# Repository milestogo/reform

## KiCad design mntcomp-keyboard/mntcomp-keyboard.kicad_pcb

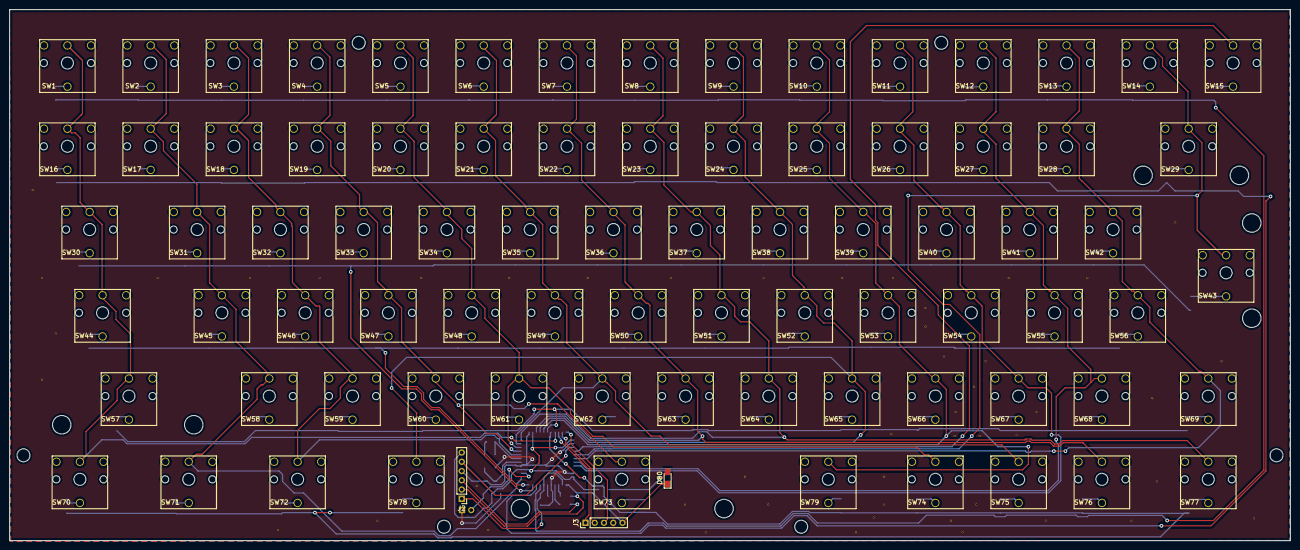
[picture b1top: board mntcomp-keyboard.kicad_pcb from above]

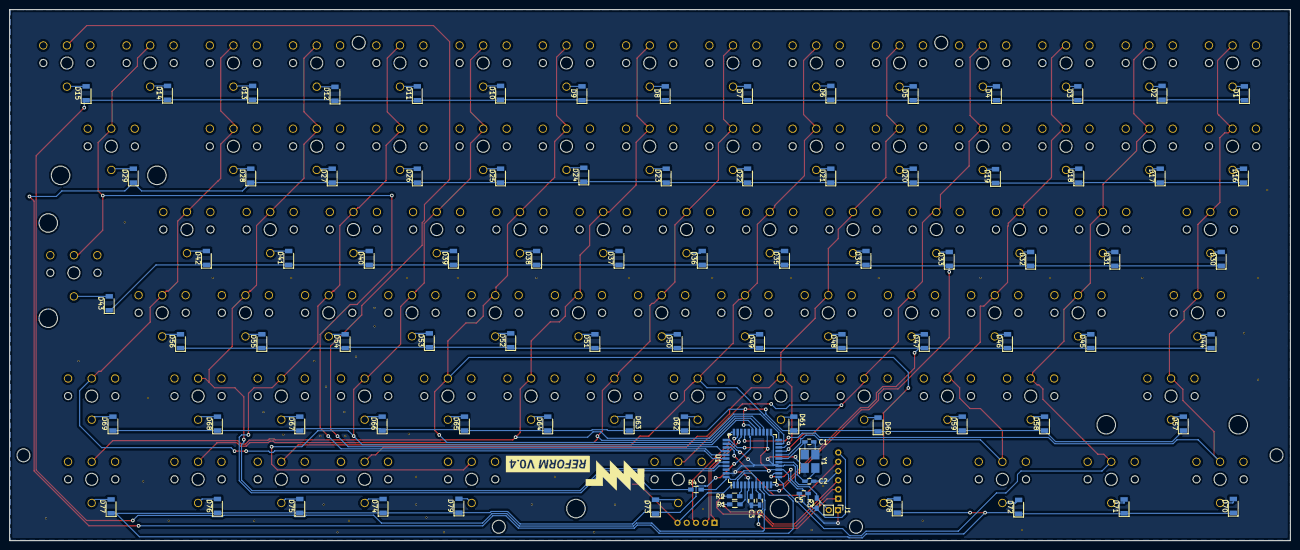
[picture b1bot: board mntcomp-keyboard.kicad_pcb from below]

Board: 2 copper layers, 276.9 x 114.8 mm, 237 parts (91 on the bottom side), 117 nets.

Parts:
C1, C2: 10pF; C_0603_HandSoldering
C3, C4, C5: 1uF; C_0603_HandSoldering
D1, D2, D3, D4, D5, D6, D7, D8, D9, D10, D11, D12, D13, D14, D15, D16, D17, D18, D19, D20, D21, D22, D23, D24, D25, D26, D27, D28, D29, D30, D31, D32, D33, D34, D35, D36, D37, D38, D39, D40, D41, D42, D43, D44, D45, D46, D47, D48, D49, D50, D51, D52, D53, D54, D55, D56, D57, D58, D59, D60, D61, D62, D63, D64, D65, D66, D67, D68, D69, D70, D71, D72, D73, D74, D75, D76, D77, D78, D79: D_Small; D_1206
D80: LED; LED_0805_HandSoldering
J1: Conn_01x02; Pin_Header_Straight_1x02_Pitch2.00mm
J2: Conn_01x06; Pin_Header_Straight_1x06_Pitch2.00mm
J3: Conn_01x05; Pin_Header_Straight_1x05_Pitch2.00mm
MH1, MH2, MH3, MH4, MH5, MH6: Hole; MountingHole_3mm
R: V; VIA-0.4mm
R1, R2: 22; R_0603_HandSoldering
R3: 10k; R_0603_HandSoldering
R4: R_Small; R_0603_HandSoldering
R#2, R#3, R#4, R#5, R#6, R#7, R#8, R#9, R#10, R#11, R#12, R#13, R#14, R#15, R#16, R#17, R#18, R#19, R#20, R#21, R#22, R#23, R#24, R#25, R#26, R#27, R#28, R#29, R#30, R#31, R#32, R#33, R#34, R#35, R#36, R#37, R#38, R#39, R#40, R#41, R#42, R#43, R#44, R#45, R#46, R#47, R#48, R#49, R#50: V; VIA-0.4mm
SH1, SH2, SH3, SH4, SH5, SH6, SH7, SH8: Hole; MountingHole_4mm
SW1, SW2, SW3, SW4, SW5, SW6, SW7, SW8, SW9, SW10, SW11, SW12, SW13, SW14, SW15, SW16, SW17, SW18, SW19, SW20, SW21, SW22, SW23, SW24, SW25, SW26, SW27, SW28, SW29, SW30, SW31, SW32, SW33, SW34, SW35, SW36, SW37, SW38, SW39, SW40, SW41, SW42, SW43, SW44, SW45, SW46, SW47, SW48, SW49, SW50, SW51, SW52, SW53, SW54, SW55, SW56, SW57, SW58, SW59, SW60, SW61, SW62, SW63, SW64, SW65, SW66, SW67, SW68, SW69, SW70, SW71, SW72, SW73, SW74, SW75, SW76, SW77, SW78, SW79: ML; cherry-ml
U1: ATMEGA32U4-AU; TQFP-44_10x10mm_Pitch0.8mm
Y1: 16MHz; Crystal_SMD_3225-4pin_3.2x2.5mm_HandSoldering

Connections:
COL1: SW1.2, SW16.2, SW30.2, SW44.2, SW57.2, SW70.2, U1.30
COL2: SW2.2, SW17.2, SW31.2, SW45.2, SW58.2, SW71.2, U1.12
COL3: SW3.2, SW18.2, SW32.2, SW46.2, SW59.2, SW72.2, U1.18
COL4: SW4.2, SW19.2, SW33.2, SW47.2, SW60.2, SW73.2, U1.19
COL5: SW5.2, SW20.2, SW34.2, SW48.2, SW61.2, SW74.2, U1.20
COL6: SW6.2, SW21.2, SW35.2, SW49.2, SW62.2, SW75.2, U1.21
COL7: SW7.2, SW22.2, SW36.2, SW50.2, SW63.2, SW76.2, U1.25
COL8: SW8.2, SW23.2, SW37.2, SW51.2, SW64.2, SW77.2, U1.22
COL9: SW9.2, SW24.2, SW38.2, SW52.2, SW65.2, SW78.2, U1.26
COL10: SW10.2, SW25.2, SW39.2, SW53.2, SW66.2, SW79.2, U1.27
COL11: SW11.2, SW26.2, SW40.2, SW54.2, SW67.2, U1.41
COL12: SW12.2, SW27.2, SW41.2, SW55.2, SW68.2, U1.40
COL13: SW13.2, SW28.2, SW42.2, SW56.2, SW69.2, U1.39
COL14: SW14.2, SW29.2, SW43.2, U1.38
COL15: SW15.2, U1.37
D+: J2.3, R1.2
D-: J2.2, R2.2
GND: C1.2, C2.2, C3.2, C4.2, C5.2, J1.1, J2.4, J3.4, R.1, R#2.1, R#3.1, R#4.1, R#5.1, R#6.1, R#7.1, R#8.1, R#9.1, R#10.1, R#11.1, R#12.1, R#13.1, R#14.1, R#15.1, R#16.1, R#17.1, R#18.1, R#19.1, R#20.1, R#21.1, R#22.1, R#23.1, R#24.1, R#25.1, R#26.1, R#27.1, R#28.1, R#29.1, R#30.1, R#31.1, R#32.1, R#33.1, R#34.1, R#35.1, R#36.1, R#37.1, R#38.1, R#39.1, R#40.1, R#41.1, R#42.1, R#43.1, R#44.1, R#45.1, R#46.1, R#47.1, R#48.1, R#49.1, R#50.1, U1.5, U1.15, U1.23, U1.35, U1.43, Y1.2, Y1.4
unnamed: C1.1, U1.17, Y1.1
unnamed: C2.1, U1.16, Y1.3
unnamed: C3.1, U1.6
unnamed: D1.2, SW1.4
unnamed: D2.2, SW2.4
unnamed: D3.2, SW3.4
unnamed: D4.2, SW4.4
unnamed: D5.2, SW5.4
unnamed: D6.2, SW6.4
unnamed: D7.2, SW7.4
unnamed: D8.2, SW8.4
unnamed: D9.2, SW9.4
unnamed: D10.2, SW10.4
unnamed: D11.2, SW11.4
unnamed: D12.2, SW12.4
unnamed: D13.2, SW13.4
unnamed: D14.2, SW14.4
unnamed: D15.2, SW15.4
unnamed: D16.2, SW16.4
unnamed: D17.2, SW17.4
unnamed: D18.2, SW18.4
unnamed: D19.2, SW19.4
unnamed: D20.2, SW20.4
unnamed: D21.2, SW21.4
unnamed: D22.2, SW22.4
unnamed: D23.2, SW23.4
unnamed: D24.2, SW24.4
unnamed: D25.2, SW25.4
unnamed: D26.2, SW26.4
unnamed: D27.2, SW27.4
unnamed: D28.2, SW28.4
unnamed: D29.2, SW29.4
unnamed: D30.2, SW30.4
unnamed: D31.2, SW31.4
unnamed: D32.2, SW32.4
unnamed: D33.2, SW33.4
unnamed: D34.2, SW34.4
unnamed: D35.2, SW35.4
unnamed: D36.2, SW36.4
unnamed: D37.2, SW37.4
unnamed: D38.2, SW38.4
unnamed: D39.2, SW39.4
unnamed: D40.2, SW40.4
unnamed: D41.2, SW41.4
unnamed: D42.2, SW42.4
unnamed: D43.2, SW43.4
unnamed: D44.2, SW44.4
unnamed: D45.2, SW45.4
unnamed: D46.2, SW46.4
unnamed: D47.2, SW47.4
unnamed: D48.2, SW48.4
unnamed: D49.2, SW49.4
unnamed: D50.2, SW50.4
unnamed: D51.2, SW51.4
unnamed: D52.2, SW52.4
unnamed: D53.2, SW53.4
unnamed: D54.2, SW54.4
unnamed: D55.2, SW55.4
unnamed: D56.2, SW56.4
unnamed: D57.2, SW57.4
unnamed: D58.2, SW58.4
unnamed: D59.2, SW59.4
unnamed: D60.2, SW60.4
unnamed: D61.2, SW61.4
unnamed: D62.2, SW62.4
unnamed: D63.2, SW63.4
unnamed: D64.2, SW64.4
unnamed: D65.2, SW65.4
unnamed: D66.2, SW66.4
unnamed: D67.2, SW67.4
unnamed: D68.2, SW68.4
unnamed: D69.2, SW69.4
unnamed: D70.2, SW70.4
unnamed: D71.2, SW71.4
unnamed: D72.2, SW72.4
unnamed: D73.2, SW73.4
unnamed: D74.2, SW74.4
unnamed: D75.2, SW75.4
unnamed: D76.2, SW76.4
unnamed: D77.2, SW77.4
unnamed: D78.2, SW78.4
unnamed: D79.2, SW79.4
unnamed: D80.1, J3.5, U1.1
unnamed: D80.2, R4.1
unnamed: J3.1, U1.31
unnamed: J3.2, U1.32
unnamed: J3.3, U1.33
unnamed: R1.1, U1.4
unnamed: R2.1, U1.3
PWRON: J2.5, U1.36
RAWVCC: C5.1, J2.6, R3.1, R4.2, U1.14, U1.24, U1.34, U1.44
RESET: J1.2, R3.2, U1.13
ROW1: D1.1, D2.1, D3.1, D4.1, D5.1, D6.1, D7.1, D8.1, D9.1, D10.1, D11.1, D12.1, D13.1, D14.1, D15.1, U1.8
ROW2: D16.1, D17.1, D18.1, D19.1, D20.1, D21.1, D22.1, D23.1, D24.1, D25.1, D26.1, D27.1, D28.1, D29.1, U1.9
ROW3: D30.1, D31.1, D32.1, D33.1, D34.1, D35.1, D36.1, D37.1, D38.1, D39.1, D40.1, D41.1, D42.1, D43.1, U1.10
ROW4: D44.1, D45.1, D46.1, D47.1, D48.1, D49.1, D50.1, D51.1, D52.1, D53.1, D54.1, D55.1, D56.1, U1.11
ROW5: D57.1, D58.1, D59.1, D60.1, D61.1, D62.1, D63.1, D64.1, D65.1, D66.1, D67.1, D68.1, D69.1, U1.28
ROW6: D70.1, D71.1, D72.1, D73.1, D74.1, D75.1, D76.1, D77.1, D78.1, D79.1, U1.29
UVCC: C4.1, J2.1, U1.2, U1.7

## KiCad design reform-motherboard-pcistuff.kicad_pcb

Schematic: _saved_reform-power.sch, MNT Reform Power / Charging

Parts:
BT1: Battery_Cell; SHDR4W90P500X350_2X2_865X1100X800P
C2, C27: 4.7uF; C_0603_HandSoldering
C3, C25, C28, C34: 10uF; C_0603_HandSoldering
C18, C19, C20, C21, C22: 22uF; CP_Elec_4x5.8
C23: 47uF; CP_Elec_4x5.8
C24: 0.1uF; C_0603_HandSoldering
C26, C29: 1uF; C_0603_HandSoldering
C33: 4.7uF; C_0805_HandSoldering
D1, D4: D_Schottky; D_SOD-323_HandSoldering
D3: LED_CHRG; LED_0805_HandSoldering
J6: Barrel_Jack; SWC_RAPC712X
J22: Conn_PWRON; Pin_Header_Straight_1x02_Pitch2.54mm
L1: 1 uH; Inductor_Taiyo-Yuden_MD-4040
L2: 18 uH; Inductor_1212
R2: 1.15k; R_0603_HandSoldering
R3: 1k; R_0603_HandSoldering
R4: 5.1k; R_0603_HandSoldering
R5, R14: 2.4k; R_0603_HandSoldering
R7, R8, R9, R10, R15: 0; R_0603_HandSoldering
R11: 10k; R_0603_HandSoldering
R13: 2.1k; R_0603_HandSoldering
TP1: TEST_BAT; Measurement_Point_Round-SMD-Pad_Big
TP2: TEST_5V; Measurement_Point_Round-SMD-Pad_Big
TP3: TEST_3V3; Measurement_Point_Round-SMD-Pad_Big
TP5: TEST_2V5; Measurement_Point_Round-SMD-Pad_Big
TP11: PWRMON_ALERT; Measurement_Point_Round-SMD-Pad_Big
TP12: TEST_1V5; Measurement_Point_Round-SMD-Pad_Big
U2: MCP73123T-22SI/MF; SON50P300X300X100-11N; Digi-Key_Part_Number MCP73123T-22SI/MF-ND
U3: TPS61235RWLR; CONV_TPS61235RWLR
U4: AP1501A-33K5G-13; DPAK171P1524X485-6N
U5: SN74LVC1G14DBVR; SOT95P280X145-5N
U6, U11: TPS74801DRCR; SON50P300X300X100-11N
U7: INA260AIPW; SOP65P640X120-16N

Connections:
+1V5: C34.1, R13.1, U11.9, U11.10; also elsewhere on the board
+2V5: C28.1, R4.1, R11.1, U6.9, U6.10; also elsewhere on the board
+3V3: C22.1, C23.1, L2.2, R8.2, TP3.1, U4.4; also elsewhere on the board
+5V: C18.1, C19.1, C20.1, C21.1, C26.1, C29.1, R10.2, TP2.1, U3.6, U3.9, U4.1, U5.5, U6.1, U6.2, U11.1, U11.2; also elsewhere on the board
GND: BT1.2, C2.2, C3.2, C18.2, C19.2, C20.2, C21.2, C22.2, C23.2, C24.2, C25.2, C26.2, C27.2, C28.2, C29.2, C33.2, C34.2, D3.2, D4.2, J6.2, R2.1, R5.2, R14.2, U2.8, U2.9, U2.11, U3.1, U3.4, U3.5, U3.8, U4.3, U4.6, U5.3, U6.6, U6.7, U6.11, U7.4, U7.6, U7.11, U7.13, U11.6, U11.7, U11.11; also elsewhere on the board
I2C3_SCL: U7.9; also elsewhere on the board
I2C3_SDA: U7.8; also elsewhere on the board
JACK_SENSE: J6.3
unnamed: BT1.1, C2.1, D1.2, TP1.1, U2.3, U2.4
unnamed: C3.1, J22.1, L1.1, U3.3, U7.14, U7.15, U7.16
unnamed: C24.1, R7.1, U7.5, U7.10
unnamed: C25.1, D1.1, J6.1, R7.2, U2.1, U2.2, U7.1, U7.2, U7.3, U7.12
unnamed: C27.1, U6.4
unnamed: C33.1, U11.4
unnamed: D3.1, R3.1
unnamed: D4.1, L2.1, U4.2
unnamed: L1.2, U3.2
unnamed: R2.2, U2.10
unnamed: R3.2, U2.7
unnamed: R4.2, R5.1, TP5.1, U6.8
unnamed: R9.1, U6.5
unnamed: R13.2, R14.1, TP12.1, U11.8
unnamed: R15.1, U11.5
unnamed: TP11.1, U7.7
unnamed: U4.5, U5.4
POK_1V5: U11.3; also elsewhere on the board
POK_1V5_MODULE: R9.2; also elsewhere on the board
POK_2V5: R11.2, U5.2, U6.3
POK_3V3: R8.1, R15.2; also elsewhere on the board
POK_5V: R10.1; also elsewhere on the board
PWRON: J22.2, U3.7

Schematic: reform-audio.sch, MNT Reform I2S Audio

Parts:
C55, C56, C57, C58, C59, C61, C63: 0.1uF; C_0603_HandSoldering
C60, C62, C64, C65: 1uF; C_0603_HandSoldering
J16: Conn_LineIn; Pin_Header_Straight_1x03_Pitch2.00mm
J17: Conn_LineOut; Pin_Header_Straight_1x03_Pitch2.00mm
J18: TRRS; SJ-43516-SMT
R31: 2.2k; R_0603_HandSoldering
U10: SGTL5000XNAA3; QFN50P500X500X100-33N

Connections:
+1V5: C59.2, C61.2, U10.5, U10.30; also elsewhere on the board
+3V3: C63.2, U10.20; also elsewhere on the board
AUD4_CLK: U10.21; also elsewhere on the board
AUD4_RXD: U10.25; also elsewhere on the board
AUD4_TXC: U10.24; also elsewhere on the board
AUD4_TXD: U10.26; also elsewhere on the board
AUD4_TXFS: U10.23; also elsewhere on the board
GND: C55.1, C56.1, C58.1, C59.1, C61.1, C63.1, J16.3, J17.3, U10.1, U10.3, U10.7, U10.31, U10.32, U10.EXP; also elsewhere on the board
I2C3_SCL: U10.29; also elsewhere on the board
I2C3_SDA: U10.27; also elsewhere on the board
unnamed: C55.2, U10.10
unnamed: C56.2, R31.2, U10.16
unnamed: C57.1, U10.15
unnamed: C57.2, J18.4, R31.1
unnamed: C58.2, U10.18
unnamed: C60.1, U10.14
unnamed: C60.2, J16.1
unnamed: C62.1, U10.13
unnamed: C62.2, J16.2
unnamed: C64.1, J17.2
unnamed: C64.2, U10.11
unnamed: C65.1, J17.1
unnamed: C65.2, U10.12
unnamed: J18.1, U10.6
unnamed: J18.2, U10.2
unnamed: J18.3, U10.4

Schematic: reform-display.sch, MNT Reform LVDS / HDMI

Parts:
C67, C68: 10uF; C_0603_HandSoldering
C69, C70, C71, C72, C73: 0.1uF; C_0603_HandSoldering
D6: D_Schottky; D_SOD-323_HandSoldering
J13: Conn_HDMI; 685119134923
J14: Conn_LVDS; Pin_Header_Angled_2x10_Pitch2.00mm
J26: Conn_Backlight; Pin_Header_Angled_1x06_Pitch2.00mm
R35: R0; R_0603_HandSoldering
R36: 47k; R_0603_HandSoldering
R37: 27k; R_0603_HandSoldering
R38, R39: 4.99k; R_0603_HandSoldering
R40: 15k; R_0603_HandSoldering
U14: CM2020-00TR; TSSOP50P640X120-38N

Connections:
+3V3: C68.1, C69.1, D6.2, J14.1, J14.2, J14.3, R35.2, U14.2; also elsewhere on the board
+5V: C67.1, C70.1, J26.1, U14.1; also elsewhere on the board
GND: C67.2, C68.2, C69.2, C70.2, C71.2, C72.2, C73.2, J13.2, J13.5, J13.8, J13.11, J13.17, J14.5, J14.6, J26.6, R40.2, U14.3, U14.5, U14.8, U14.11, U14.14, U14.25, U14.28, U14.31, U14.34, U14.36; also elsewhere on the board
HDMI_CEC_IN: U14.16; also elsewhere on the board
HDMI_CLK_N: J13.12, U14.15, U14.24; also elsewhere on the board
HDMI_CLK_P: J13.10, U14.13, U14.26; also elsewhere on the board
HDMI_D0_N: J13.9, U14.12, U14.27; also elsewhere on the board
HDMI_D0_P: J13.7, U14.10, U14.29; also elsewhere on the board
HDMI_D1_N: J13.6, U14.9, U14.30; also elsewhere on the board
HDMI_D1_P: J13.4, U14.7, U14.32; also elsewhere on the board
HDMI_D2_N: J13.3, U14.6, U14.33; also elsewhere on the board
HDMI_D2_P: J13.1, U14.4, U14.35; also elsewhere on the board
HDMI_HPD: R36.1, U14.19; also elsewhere on the board
I2C1_SCL: U14.17; also elsewhere on the board
I2C1_SDA: U14.18; also elsewhere on the board
LVDS0_CLK_N: J14.15; also elsewhere on the board
LVDS0_CLK_P: J14.16; also elsewhere on the board
LVDS0_PWM: J26.4; also elsewhere on the board
LVDS0_TX0_N: J14.7; also elsewhere on the board
LVDS0_TX0_P: J14.8; also elsewhere on the board
LVDS0_TX1_N: J14.9; also elsewhere on the board
LVDS0_TX1_P: J14.10; also elsewhere on the board
LVDS0_TX2_N: J14.11; also elsewhere on the board
LVDS0_TX2_P: J14.12; also elsewhere on the board
LVDS0_TX3_N: J14.19; also elsewhere on the board
LVDS0_TX3_P: J14.20; also elsewhere on the board
unnamed: C71.1, U14.37
unnamed: C72.1, J13.19, R40.1, U14.20
unnamed: C73.1, J13.18, R36.2, R38.2, R39.2, U14.38
unnamed: D6.1, R37.2
unnamed: J13.13, R37.1, U14.23
unnamed: J13.15, R38.1, U14.22
unnamed: J13.16, R39.1, U14.21
unnamed: J26.3, R35.1

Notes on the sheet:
LCD Screen
HDMI

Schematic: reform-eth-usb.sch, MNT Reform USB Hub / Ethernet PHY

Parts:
C13, C14, C15, C16, C17, C38, C39, C42, C43, C44, C45, C46, C47, C48, C49, C50, C51, C52, C54: 0.1uF; C_0603_HandSoldering
C36, C37: 0.001uF; C_0603_HandSoldering
C40, C41: 18pF; C_0603_HandSoldering
C53: 1uF; C_0603_HandSoldering
J5, J7: USB_A
J9: USB_INT_1; Pin_Header_Angled_1x04_Pitch2.00mm
J12: USB_INT_3; Pin_Header_Angled_1x04_Pitch2.00mm
J15: USB_INT_2; Pin_Header_Angled_1x04_Pitch2.00mm
P2: J0G-0003NL; PULSE_J0G-0003NL
R16, R17: 1M; R_0603_HandSoldering
R18, R19, R23, R24, R25, R26, R27, R28, R29: 4.7k; R_0603_HandSoldering
R20: 9.53k 1%; R_0603_HandSoldering
R21: 90.9 1%; R_0603_HandSoldering
R22: 10k 1%; R_0603_HandSoldering
R30: 10M; R_0603_HandSoldering
U8: TUSB4041IPAPR; QFP50P1200X1200X105-65N
U9: TLV71311PDBV; SOT-23-5
Y1: 24MHz; Crystal_SMD_Abracon_ABM3-2pin_5.0x3.2mm_HandSoldering

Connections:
+1V1: C42.1, C44.1, C47.1, C49.1, C51.1, C52.1, C53.1, C54.1, U8.19, U8.25, U8.37, U8.45, U8.53, U8.60, U8.63, U9.5 (OUT)
+3V3: C13.1, C43.1, C45.1, C46.1, C48.1, C50.1, P2.14, P2.16, R29.2, U8.2, U8.20, U8.31, U8.48, U9.1 (IN), U9.3 (EN); also elsewhere on the board
+5V: J5.1, J7.1, J9.1, J12.1, J15.1, R21.1; also elsewhere on the board
ENET_LED_LINK: P2.13; also elsewhere on the board
ENET_LED_RX: P2.17; also elsewhere on the board
GND: C13.2, C14.2, C15.2, C16.2, C17.2, C36.2, C37.2, C38.2, C39.2, C40.2, C41.2, C42.2, C43.2, C44.2, C45.2, C46.2, C47.2, C48.2, C49.2, C50.2, C51.2, C52.2, C53.2, C54.2, J5.4, J7.4, J9.4, J12.4, J15.4, P2.SH1, P2.SH2, R16.2, R17.2, R18.2, R19.2, R20.2, R22.2, R23.2, R24.2, R25.2, R26.2, R27.2, R28.2, U8.65, U9.2 (GND); also elsewhere on the board
unnamed: C14.1, P2.7
unnamed: C15.1, P2.1
unnamed: C16.1, P2.6
unnamed: C17.1, P2.12
unnamed: C36.1, C38.1, J5.5, R16.1
unnamed: C37.1, C39.1, J7.5, R17.1
unnamed: C40.1, R30.1, U8.30, Y1.1
unnamed: C41.1, R30.2, U8.29, Y1.2
unnamed: J5.2, U8.34
unnamed: J5.3, U8.33
unnamed: J7.2, U8.42
unnamed: J7.3, U8.41
unnamed: J12.2, U8.50
unnamed: J12.3, U8.49
unnamed: J15.2, U8.57
unnamed: J15.3, U8.56
unnamed: R18.1, U8.4
unnamed: R19.1, U8.3
unnamed: R20.1, U8.32
unnamed: R21.2, R22.1, U8.16
unnamed: R23.1, U8.1
unnamed: R24.1, U8.64
unnamed: R25.1, U8.17
unnamed: R26.1, U8.13
unnamed: R27.1, U8.10
unnamed: R28.1, U8.9
unnamed: R29.1, U8.8
RESET: U8.18; also elsewhere on the board
TRD0_N: P2.10; also elsewhere on the board
TRD0_P: P2.11; also elsewhere on the board
TRD1_N: P2.5; also elsewhere on the board
TRD1_P: P2.4; also elsewhere on the board
TRD2_N: P2.2; also elsewhere on the board
TRD2_P: P2.3; also elsewhere on the board
TRD3_N: P2.9; also elsewhere on the board
TRD3_P: P2.8; also elsewhere on the board
USB0_N: J9.2; also elsewhere on the board
USB0_P: J9.3; also elsewhere on the board
USB1_N: U8.22; also elsewhere on the board
USB1_P: U8.21; also elsewhere on the board

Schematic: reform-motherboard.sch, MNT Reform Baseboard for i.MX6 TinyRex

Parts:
C11: 0.1uF; C_0603_HandSoldering
C12: 22uF; C_0805_HandSoldering
J1: TinyRex-J1-DF40C; HRS_DF40C-100DS-0.4V(51); Digi-Key_Part_Number H11615CT-ND
J2: TinyRex-J2-DF40C; HRS_DF40C-100DS-0.4V(51); Digi-Key_Part_Number H11615CT-ND
J3: TinyRex-J3-DF40C; HRS_DF40C-100DS-0.4V(51); Digi-Key_Part_Number H11615CT-ND
J8: TEST_BM0; Measurement_Point_Round-SMD-Pad_Small
J10: TEST_PMIC_ON; Measurement_Point_Round-SMD-Pad_Small
J11: TEST_ON; Measurement_Point_Round-SMD-Pad_Small
J20: Conn_GPIO1; Pin_Header_Straight_1x04_Pitch2.00mm
J21: Conn_SPI2; Pin_Header_Straight_1x06_Pitch2.00mm
J35: Conn_SPI1; Pin_Header_Straight_1x06_Pitch2.00mm
MH1, MH2, MH3, MH4: BoardMount; MountingHole_3.2mm_M3_Pad
MH5, MH6: ModuleMount; MountingHole_2.2mm_M2
R6: 0; R_0603_HandSoldering
TP13: TEST_1V2; Measurement_Point_Round-SMD-Pad_Small

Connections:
+2V5: J3.48, J3.58; also elsewhere on the board
+3V3: J1.22, J1.24, J1.42, J1.44, J1.46; also elsewhere on the board
+5V: C11.1, C12.1, J1.1, J1.2, J1.3, J1.4, J1.6, J1.8, J1.10, J1.12, J1.14, J1.16, J1.18, J1.20, J1.76, J1.84; also elsewhere on the board
AUD4_CLK: J2.14; also elsewhere on the board
AUD4_RXD: J2.22; also elsewhere on the board
AUD4_TXC: J2.16; also elsewhere on the board
AUD4_TXD: J2.20; also elsewhere on the board
AUD4_TXFS: J2.18; also elsewhere on the board
ENET_LED_LINK: J3.14; also elsewhere on the board
ENET_LED_RX: J3.16; also elsewhere on the board
GND: C11.2, C12.2, J1.5, J1.7, J1.9, J1.11, J1.13, J1.15, J1.17, J1.19, J1.21, J1.23, J1.29, J1.30, J1.35, J1.36, J1.41, J1.49, J1.56, J1.59, J1.66, J1.83, J1.89, J1.90, J1.95, J1.96, J2.11, J2.12, J2.24, J2.31, J2.34, J2.40, J2.41, J2.46, J2.51, J2.56, J2.65, J2.71, J2.77, J2.78, J2.83, J2.84, J2.89, J2.90, J3.5, J3.11, J3.25, J3.28, J3.35, J3.38, J3.45, J3.55, J3.68, J3.69, J3.79, J3.80, J3.91, J3.92, J20.1, J20.6, J21.1, J21.6, J21.11, MH1.1, MH2.1, MH3.1, MH4.1, MH5.1, MH6.1, R6.1; also elsewhere on the board
HDMI_CEC_IN: J1.80; also elsewhere on the board
HDMI_CEC_STBY: J1.82
HDMI_CLK_N: J1.92; also elsewhere on the board
HDMI_CLK_P: J1.94; also elsewhere on the board
HDMI_D0_N: J1.86; also elsewhere on the board
HDMI_D0_P: J1.88; also elsewhere on the board
HDMI_D1_N: J1.79; also elsewhere on the board
HDMI_D1_P: J1.81; also elsewhere on the board
HDMI_D2_N: J1.85; also elsewhere on the board
HDMI_D2_P: J1.87; also elsewhere on the board
HDMI_HPD: J1.78; also elsewhere on the board
I2C1_SCL: J2.26; also elsewhere on the board
I2C1_SDA: J2.28; also elsewhere on the board
I2C2_SCL: J2.48; also elsewhere on the board
I2C2_SDA: J2.50; also elsewhere on the board
I2C3_SCL: J2.54; also elsewhere on the board
I2C3_SDA: J2.52; also elsewhere on the board
LVDS0_CABC: J1.40
LVDS0_CLK_N: J1.25; also elsewhere on the board
LVDS0_CLK_P: J1.27; also elsewhere on the board
LVDS0_PWM: J1.38; also elsewhere on the board
LVDS0_TX0_N: J1.26; also elsewhere on the board
LVDS0_TX0_P: J1.28; also elsewhere on the board
LVDS0_TX1_N: J1.32; also elsewhere on the board
LVDS0_TX1_P: J1.34; also elsewhere on the board
LVDS0_TX2_N: J1.31; also elsewhere on the board
LVDS0_TX2_P: J1.33; also elsewhere on the board
LVDS0_TX3_N: J1.37; also elsewhere on the board
LVDS0_TX3_P: J1.39; also elsewhere on the board
unnamed: J1.69, J1.77, J8.1
unnamed: J2.13, J20.10
unnamed: J2.15, J20.9
unnamed: J2.17, J20.8
unnamed: J2.19, J20.7
unnamed: J2.23, J20.5
unnamed: J2.25, J20.4
unnamed: J2.27, J20.3
unnamed: J2.29, J20.2
unnamed: J2.66, J2.68, R6.2
unnamed 131: J2.72; also elsewhere on the board
unnamed 132: J2.74; also elsewhere on the board
unnamed: J3.6, J3.12, J3.20, TP13.1
unnamed: J2.6, J10.1
unnamed: J2.8, J11.1
unnamed 215: J2.3; also elsewhere on the board
unnamed: J3.50, J21.2
unnamed: J3.52, J21.3
unnamed: J3.54, J21.4
unnamed: J3.56, J21.5
unnamed: J3.60, J21.7
unnamed: J3.62, J21.8
unnamed: J3.64, J21.9
unnamed: J3.66, J21.10
unnamed: J3.70, J21.12
unnamed: J3.72, J21.13
unnamed: J3.74, J21.14
unnamed: J3.76, J21.15
unnamed: J3.78, J21.16
PCIE_CLK_N: J2.80; also elsewhere on the board
PCIE_CLK_P: J2.82; also elsewhere on the board
PCIE_RX_N: J2.85; also elsewhere on the board
PCIE_RX_P: J2.87; also elsewhere on the board
PCIE_TX_N: J2.79; also elsewhere on the board
PCIE_TX_P: J2.81; also elsewhere on the board
PCIE_WAKE: J2.76; also elsewhere on the board
POK_1V5_MODULE: J2.5; also elsewhere on the board
POK_3V3: J2.9; also elsewhere on the board
POK_5V: J2.7; also elsewhere on the board
RSTINn: J2.2; also elsewhere on the board
RSTOUTn: J2.4; also elsewhere on the board
SATA_RX_N: J2.36; also elsewhere on the board
SATA_RX_P: J2.38; also elsewhere on the board
SATA_TX_N: J2.42; also elsewhere on the board
SATA_TX_P: J2.44; also elsewhere on the board
SD1_CD: J3.67
SD1_CLK: J3.89
SD1_CMD: J3.90
SD1_DATA0: J3.82
SD1_DATA1: J3.84
SD1_DATA2: J3.86
SD1_DATA3: J3.88
SD1_DATA4: J3.81
SD1_DATA5: J3.83
SD1_DATA6: J3.85
SD1_DATA7: J3.87
SD1_WP: J3.65
SD3_CD: J2.33; also elsewhere on the board
SD3_CLK: J2.37; also elsewhere on the board
SD3_CMD: J2.39; also elsewhere on the board
SD3_DATA0: J2.43; also elsewhere on the board
SD3_DATA1: J2.45; also elsewhere on the board
SD3_DATA2: J2.47; also elsewhere on the board
SD3_DATA3: J2.49; also elsewhere on the board
SD3_WP: J2.35; also elsewhere on the board
TRD0_N: J3.1; also elsewhere on the board
TRD0_P: J3.3; also elsewhere on the board
TRD1_N: J3.7; also elsewhere on the board
TRD1_P: J3.9; also elsewhere on the board
TRD2_N: J3.2; also elsewhere on the board
TRD2_P: J3.4; also elsewhere on the board
TRD3_N: J3.8; also elsewhere on the board
TRD3_P: J3.10; also elsewhere on the board
UART1_CTS: J2.59; also elsewhere on the board
UART1_RTS: J2.57; also elsewhere on the board
UART1_RXD: J2.55; also elsewhere on the board
UART1_TXD: J2.53; also elsewhere on the board
USB0_N: J2.73; also elsewhere on the board
USB0_P: J2.75; also elsewhere on the board
USB1_N: J2.67; also elsewhere on the board
USB1_P: J2.69; also elsewhere on the board
USB_OC: J2.70

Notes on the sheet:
host mode

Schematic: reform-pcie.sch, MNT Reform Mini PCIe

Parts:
C4, C5, C6, C7, C8, C9, C30: 0.1uF; C_0603_HandSoldering
C10: 4.7uF; C_0603_HandSoldering
C31, C32: 330uF; CP_Elec_6.3x7.7
J27: 48099-5701; MOLEX_48099-5701
TP6: PCIe_WLANn; Measurement_Point_Round-SMD-Pad_Small
TP7: PCIe_WDISn; Measurement_Point_Round-SMD-Pad_Small
TP8: PCIe_USB_D-; Measurement_Point_Round-SMD-Pad_Small
TP9: PCIe_USB_D+; Measurement_Point_Round-SMD-Pad_Small
U1: MPCIE-Socket; mpcie-socket

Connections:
+1V5: C7.2, C8.2, C9.2, C10.2, U1.6, U1.28, U1.48; also elsewhere on the board
+3V3: C4.1, C5.1, C6.1, C30.1, C31.1, C32.1, U1.2, U1.24, U1.39, U1.41, U1.52; also elsewhere on the board
GND: C4.2, C5.2, C6.2, C7.1, C8.1, C9.1, C10.1, C30.2, C31.2, C32.2, U1.4, U1.9, U1.15, U1.18, U1.21, U1.26, U1.27, U1.29, U1.34, U1.35, U1.37, U1.40, U1.43, U1.50; also elsewhere on the board
unnamed: TP6.1, U1.44
unnamed: TP7.1, U1.20
unnamed: TP8.1, U1.36
unnamed: TP9.1, U1.38
PCIE_CLK_N: U1.11; also elsewhere on the board
PCIE_CLK_P: U1.13; also elsewhere on the board
PCIE_RX_N: U1.23; also elsewhere on the board
PCIE_RX_P: U1.25; also elsewhere on the board
PCIE_SMB_CLK: U1.30
PCIE_SMB_DATA: U1.32
PCIE_TX_N: U1.31; also elsewhere on the board
PCIE_TX_P: U1.33; also elsewhere on the board
PCIE_WAKE: U1.1; also elsewhere on the board
RESET: U1.22; also elsewhere on the board

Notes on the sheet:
mPCIe Latch

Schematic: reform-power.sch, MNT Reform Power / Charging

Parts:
BT1: Battery_Cell; SHDR4W90P500X350_2X2_865X1100X800P
C2, C27: 4.7uF; C_0603_HandSoldering
C3, C25, C28, C34: 10uF; C_0603_HandSoldering
C18, C19, C20, C21, C22: 22uF; CP_Elec_4x5.8
C23: 47uF; CP_Elec_4x5.8
C24: 0.1uF; C_0603_HandSoldering
C26, C29: 1uF; C_0603_HandSoldering
C33: 4.7uF; C_0805_HandSoldering
D1, D4: D_Schottky; D_SOD-323_HandSoldering
D3: LED_CHRG; LED_0805_HandSoldering
J6: Barrel_Jack; SWC_RAPC712X
J22: Conn_PWRON; Pin_Header_Straight_1x02_Pitch2.54mm
L1: 1 uH; Inductor_Taiyo-Yuden_MD-4040
L2: 18 uH; Inductor_1212
R2: 1.15k; R_0603_HandSoldering
R3: 1k; R_0603_HandSoldering
R4: 5.1k; R_0603_HandSoldering
R5, R14: 2.4k; R_0603_HandSoldering
R7, R8, R9, R10, R15: 0; R_0603_HandSoldering
R11: 10k; R_0603_HandSoldering
R13: 2.1k; R_0603_HandSoldering
TP1: TEST_BAT; Measurement_Point_Round-SMD-Pad_Big
TP2: TEST_5V; Measurement_Point_Round-SMD-Pad_Big
TP3: TEST_3V3; Measurement_Point_Round-SMD-Pad_Big
TP5: TEST_2V5; Measurement_Point_Round-SMD-Pad_Big
TP11: PWRMON_ALERT; Measurement_Point_Round-SMD-Pad_Big
TP12: TEST_1V5; Measurement_Point_Round-SMD-Pad_Big
U2: MCP73123T-22SI/MF; SON50P300X300X100-11N; Digi-Key_Part_Number MCP73123T-22SI/MF-ND
U3: TPS61235RWLR; CONV_TPS61235RWLR
U4: AP1501A-33K5G-13; DPAK171P1524X485-6N
U5: SN74LVC1G14DBVR; SOT95P280X145-5N
U6, U11: TPS74801DRCR; SON50P300X300X100-11N
U7: INA260AIPW; SOP65P640X120-16N

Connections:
+1V5: C34.1, R13.1, U11.9, U11.10; also elsewhere on the board
+2V5: C28.1, R4.1, R11.1, U6.9, U6.10; also elsewhere on the board
+3V3: C22.1, C23.1, L2.2, R8.2, TP3.1, U4.4; also elsewhere on the board
+5V: C18.1, C19.1, C20.1, C21.1, C26.1, C29.1, R10.2, TP2.1, U3.6, U3.9, U4.1, U5.5, U6.1, U6.2, U11.1, U11.2; also elsewhere on the board
GND: BT1.2, C2.2, C3.2, C18.2, C19.2, C20.2, C21.2, C22.2, C23.2, C24.2, C25.2, C26.2, C27.2, C28.2, C29.2, C33.2, C34.2, D3.2, D4.2, J6.2, R2.1, R5.2, R14.2, U2.8, U2.9, U2.11, U3.1, U3.4, U3.5, U3.8, U4.3, U4.6, U5.3, U6.6, U6.7, U6.11, U7.4, U7.6, U7.11, U7.13, U11.6, U11.7, U11.11; also elsewhere on the board
I2C3_SCL: U7.9; also elsewhere on the board
I2C3_SDA: U7.8; also elsewhere on the board
JACK_SENSE: J6.3
unnamed: BT1.1, C2.1, D1.2, TP1.1, U2.3, U2.4
unnamed: C3.1, J22.1, L1.1, U3.3, U7.14, U7.15, U7.16
unnamed: C24.1, R7.1, U7.5, U7.10
unnamed: C25.1, D1.1, J6.1, R7.2, U2.1, U2.2, U7.1, U7.2, U7.3, U7.12
unnamed: C27.1, U6.4
unnamed: C33.1, U11.4
unnamed: D3.1, R3.1
unnamed: D4.1, L2.1, U4.2
unnamed: L1.2, U3.2
unnamed: R2.2, U2.10
unnamed: R3.2, U2.7
unnamed: R4.2, R5.1, TP5.1, U6.8
unnamed: R9.1, U6.5
unnamed: R13.2, R14.1, TP12.1, U11.8
unnamed: R15.1, U11.5
unnamed: TP11.1, U7.7
unnamed: U4.5, U5.4
POK_1V5: U11.3; also elsewhere on the board
POK_1V5_MODULE: R9.2; also elsewhere on the board
POK_2V5: R11.2, U5.2, U6.3
POK_3V3: R8.1, R15.2; also elsewhere on the board
POK_5V: R10.1; also elsewhere on the board
PWRON: J22.2, U3.7

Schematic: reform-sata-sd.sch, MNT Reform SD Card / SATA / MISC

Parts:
C1, C35, C66: 0.1uF; C_0603_HandSoldering
D2: LED_1V5; LED_0805_HandSoldering
D5: LED_3V3; LED_0805_HandSoldering
J4: 693072010801
J23: Conn_RESET; Pin_Header_Straight_1x02_Pitch2.54mm
J24: Conn_01x04; Pin_Header_Straight_1x04_Pitch2.00mm
J25: Conn_CONSOLE; Pin_Header_Angled_1x06_Pitch2.54mm
P1: 5622-4100-ML; 3M_5622-4100-ML
Q1, Q2, Q3: 2N7002; SOT-23
R1: 0; R_0603_HandSoldering
R12, R32, R41: 10k; R_0603_HandSoldering
R33, R34: 240; R_0603_HandSoldering
U12: SN74LVC1G08DCKR; SOT65P210X110-5N; Digi-Key_Part_Number 296-11602-1-ND
U13: TXB0104D; SOIC-14_3.9x8.7mm_Pitch1.27mm

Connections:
+3V3: C1.1, C35.1, D2.2, D5.2, J4.4, J24.1, P1.P1, P1.P2, P1.P3, R12.1, R32.1, U12.5, U13.1; also elsewhere on the board
+5V: C66.1, J25.1, P1.P7, P1.P8, P1.P9, U13.14; also elsewhere on the board
GND: C1.2, C35.2, C66.2, J4.6, J4.Z1, J4.Z2, J23.1, J24.4, J25.6, P1.P4, P1.P5, P1.P6, P1.P10, P1.P12, P1.S1, P1.S4, P1.S7, Q1.2, Q2.2, Q3.2, R1.2, R41.2, U12.3, U13.7; also elsewhere on the board
I2C2_SCL: J24.2; also elsewhere on the board
I2C2_SDA: J24.3; also elsewhere on the board
unnamed: D2.1, R33.1
unnamed: D5.1, R34.1
unnamed: J4.Z3, J4.Z4, Q1.1, R12.2
unnamed: J25.2, U13.13
unnamed: J25.3, U13.12
unnamed: J25.4, U13.11
unnamed: J25.5, U13.10
unnamed: Q2.3, R33.2
unnamed: Q3.3, R34.2
unnamed: R41.1, U13.8
POK_1V5: Q2.1; also elsewhere on the board
POK_3V3: Q3.1; also elsewhere on the board
RESET: U12.4; also elsewhere on the board
RSTINn: J23.2, R32.2; also elsewhere on the board
RSTOUTn: U12.1, U12.2; also elsewhere on the board
SATA_RX_N: P1.S5; also elsewhere on the board
SATA_RX_P: P1.S6; also elsewhere on the board
SATA_TX_N: P1.S3; also elsewhere on the board
SATA_TX_P: P1.S2; also elsewhere on the board
SD3_CD: Q1.3; also elsewhere on the board
SD3_CLK: J4.5; also elsewhere on the board
SD3_CMD: J4.3; also elsewhere on the board
SD3_DATA0: J4.7; also elsewhere on the board
SD3_DATA1: J4.8; also elsewhere on the board
SD3_DATA2: J4.1; also elsewhere on the board
SD3_DATA3: J4.2; also elsewhere on the board
SD3_WP: R1.1; also elsewhere on the board
UART1_CTS: U13.5; also elsewhere on the board
UART1_RTS: U13.4; also elsewhere on the board
UART1_RXD: U13.3; also elsewhere on the board
UART1_TXD: U13.2; also elsewhere on the board

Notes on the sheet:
Reset
Console with Level Translation
LEDs
Boot SD Card

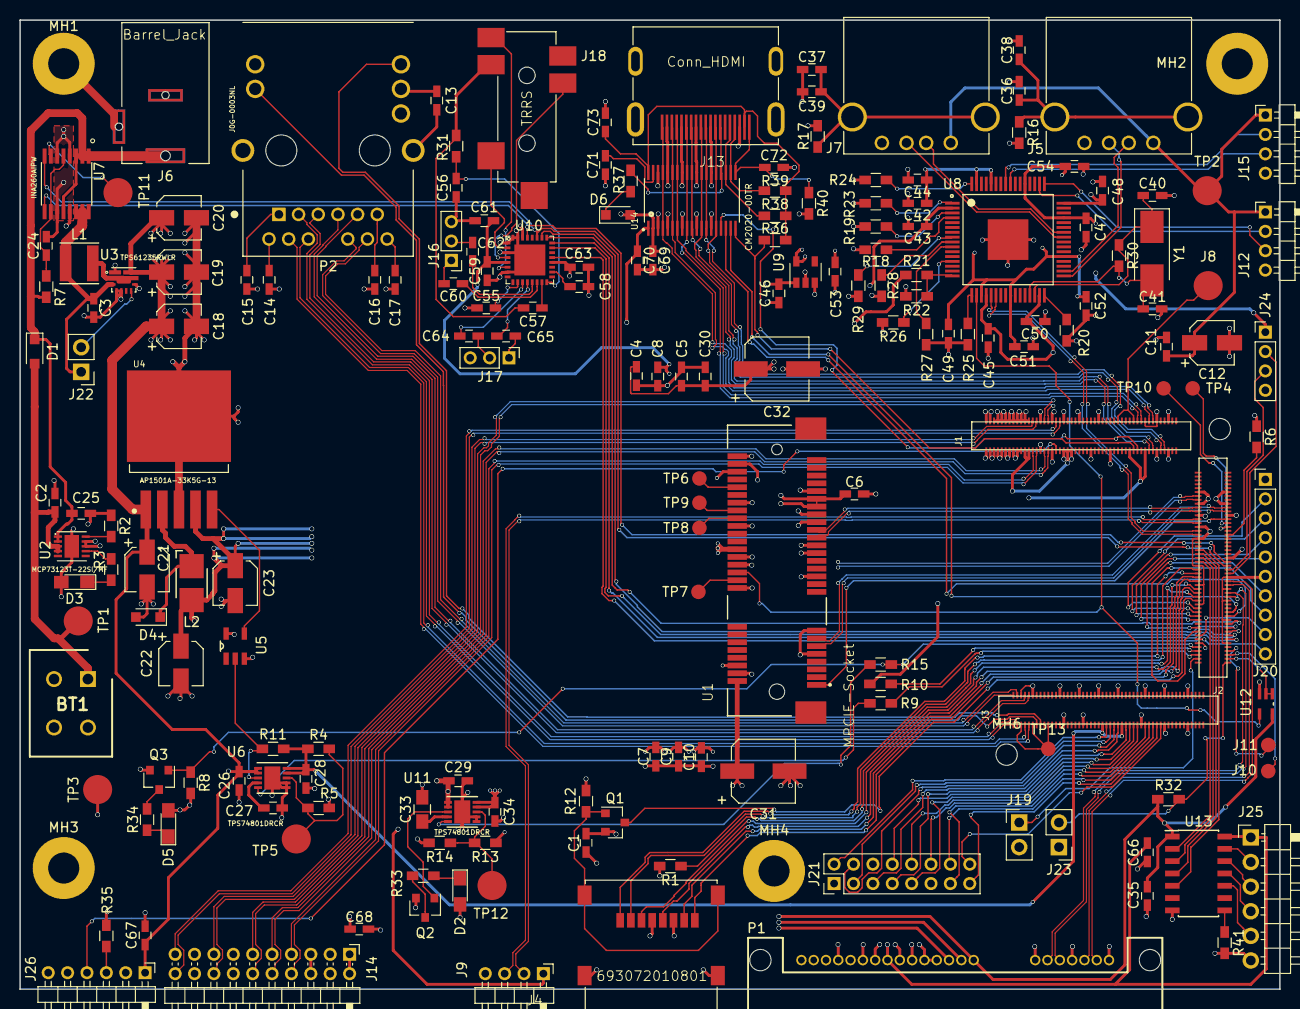
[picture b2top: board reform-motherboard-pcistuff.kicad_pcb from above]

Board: 4 copper layers, 130.0 x 100.0 mm, 188 parts (0 on the bottom side), 195 nets.

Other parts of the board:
J19: Conn_BOOT; Pin_Header_Straight_1x02_Pitch2.54mm
TP4: TEST_USB1PWR; Measurement_Point_Round-SMD-Pad_Small
TP10: TEST_USB0PWR; Measurement_Point_Round-SMD-Pad_Small

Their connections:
GND: J19.2; also elsewhere on the board
unnamed 131: TP4.1; also elsewhere on the board
unnamed 132: TP10.1; also elsewhere on the board
unnamed 215: J19.1; also elsewhere on the board

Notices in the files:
_saved_reform-power.sch:
Copyright 2017 Lukas F. Hartmann / @mntmn
License: CC BY-SA 4.0 https://creativecommons.org/licenses/by-sa/4.0
reform-motherboard.sch:
Copyright 2017,2018 Lukas F. Hartmann / @mntmn
License: GPLv3 https://www.gnu.org/licenses/gpl-3.0.txt
reform2-motherboard/reform2-motherboard/reform2-motherboard.kicad_pcb:
MNT REFORM 2.0D-1 GPLV3+
reform2-trackball/reform-trackball.sch:
License: GPLv3+ https://www.gnu.org/licenses/gpl-3.0.en.html
